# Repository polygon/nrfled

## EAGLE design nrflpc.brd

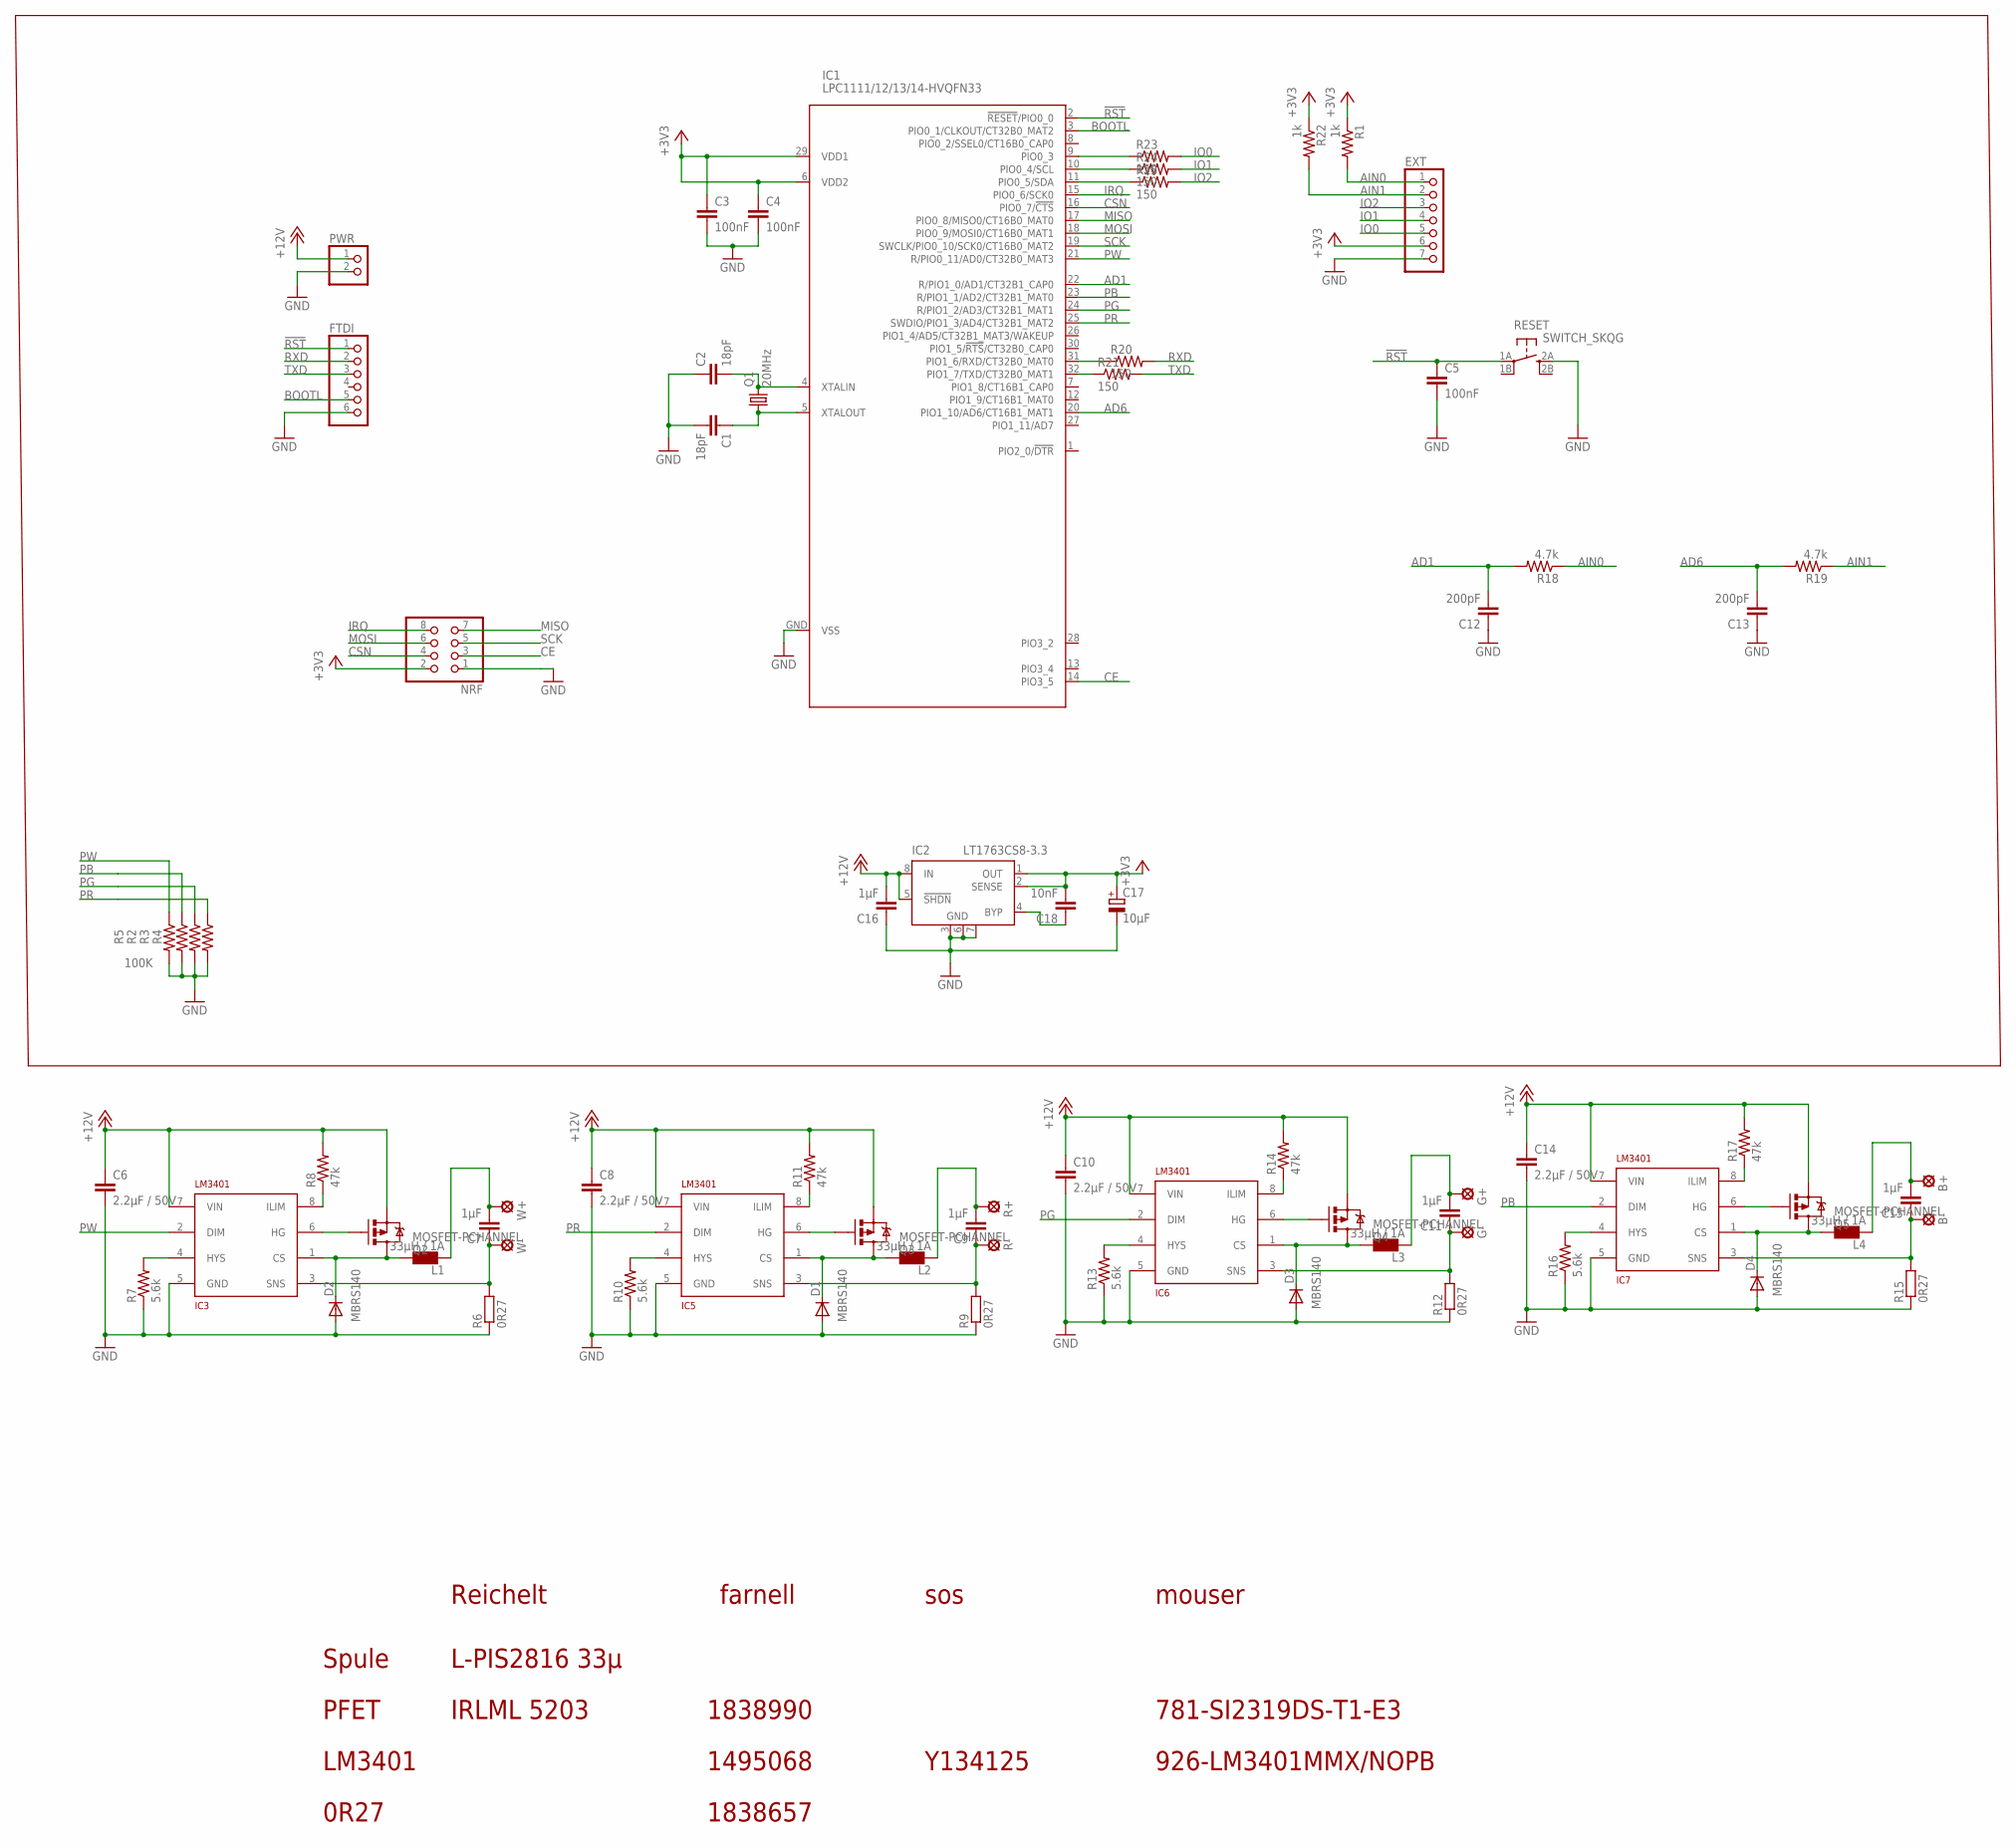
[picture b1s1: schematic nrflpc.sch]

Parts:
B+: SE14
B-: SE14
C1, C2: 18pF; 0402-CAP
C3, C4, C5: 100nF; 0402-CAP
C6, C8, C10, C14: 2.2µF / 50V; C1210
C7, C9, C11, C15, C16: 1µF; 0805
C12, C13: 200pF; 0402-CAP
C17: 10µF; SMC_A
C18: 10nF; 0402-CAP
D1, D2, D3, D4: MBRS140; SMB
EXT: PINHD-1X7; 1X07
FTDI: PINHD-1X6; 1X06
G+: SE14
G-: SE14
IC1: LPC1111/12/13/14-HVQFN33; HVQFN33
IC2: LT1763CS8-3.3; SOIC8
IC3, IC5, IC6, IC7: LM3401; MSOP8
L1, L2, L3, L4: 33µH / 1A; PIS2816
NRF: PINHD-2X4; 2X04
PWR: PINHD-1X2; 1X02
Q1: 20MHz; MT
Q2, Q3, Q4, Q5: MOSFET-PCHANNEL; SOT23
R1, R22: 1k; 0402-RES
R2, R3, R4, R5: 100K; 0402-RES
R6, R9, R12, R15: 0R27; R1206
R7, R10, R13, R16: 5.6k; 0805
R8, R11, R14, R17: 47k; 0805
R18, R19: 4.7k; 0402-RES
R20, R21, R23, R24, R25: 150; 0402-RES
R+: SE14
R-: SE14
RESET: SWITCH_SKQG
W+: SE14
W-: SE14

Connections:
!RST: C5.1, FTDI.1, IC1.2 (!RESET!/PIO0_0), RESET.1A
+3V3: C3.1, C4.1, C17.+, C18.2, EXT.6, IC1.6 (VDD2), IC1.29 (VDD1), IC2.1 (OUT), IC2.2 (SENSE), NRF.2, R1.1, R22.1
+12V: C6.1, C8.1, C10.1, C14.1, C16.2, IC2.5 (!SHDN), IC2.8 (IN), IC3.7 (VIN), IC5.7 (VIN), IC6.7 (VIN), IC7.7 (VIN), PWR.1, Q2.2 (S), Q3.2 (S), Q4.2 (S), Q5.2 (S), R8.2, R11.2, R14.2, R17.2
AD1: C12.2, IC1.22 (R/PIO1_0/AD1/CT32B1_CAP0), R18.2
AD6: C13.2, IC1.20 (PIO1_10/AD6/CT16B1_MAT1), R19.2
AIN0: EXT.1, R1.2, R18.1
AIN1: EXT.2, R19.1, R22.2
BOOTL: FTDI.5, IC1.3 (PIO0_1/CLKOUT/CT32B0_MAT2)
CE: IC1.14 (PIO3_5), NRF.3
CSN: IC1.16 (PIO0_7/!CTS!), NRF.4
GND: C1.2, C2.1, C3.2, C4.2, C5.2, C6.2, C8.2, C10.2, C12.1, C13.1, C14.2, C16.1, C17.-, D1.A, D2.A, D3.A, D4.A, EXT.7, FTDI.6, IC1.GND (VSS), IC2.3 (GND), IC2.6 (GND), IC2.7 (GND), IC3.5 (GND), IC5.5 (GND), IC6.5 (GND), IC7.5 (GND), NRF.1, PWR.2, R2.2, R3.2, R4.2, R5.2, R6.1, R7.1, R9.1, R10.1, R12.1, R13.1, R15.1, R16.1, RESET.2A
IO0: EXT.5, R23.2
IO1: EXT.4, R24.2
IO2: EXT.3, R25.2
IRQ: IC1.15 (PIO0_6/SCK0), NRF.8
MISO: IC1.17 (PIO0_8/MISO0/CT16B0_MAT0), NRF.7
MOSI: IC1.18 (PIO0_9/MOSI0/CT16B0_MAT1), NRF.6
unnamed: C7.1, IC3.3 (SNS), R6.2, W-.MP
unnamed: C7.2, L1.P$2 (2), W+.MP
unnamed: D2.C, IC3.1 (CS), L1.P$1 (1), Q2.3 (D)
unnamed: C9.1, IC5.3 (SNS), R9.2, R-.MP
unnamed: IC3.4 (HYS), R7.2
unnamed: C9.2, L2.P$2 (2), R+.MP
unnamed: IC3.8 (ILIM), R8.1
unnamed: D1.C, IC5.1 (CS), L2.P$1 (1), Q3.3 (D)
unnamed: IC5.4 (HYS), R10.2
unnamed: IC3.6 (HG), Q2.1 (G)
unnamed: IC5.8 (ILIM), R11.1
unnamed: IC5.6 (HG), Q3.1 (G)
unnamed: C11.1, G-.MP, IC6.3 (SNS), R12.2
unnamed: C11.2, G+.MP, L3.P$2 (2)
unnamed: D3.C, IC6.1 (CS), L3.P$1 (1), Q4.3 (D)
unnamed: IC6.4 (HYS), R13.2
unnamed: IC6.8 (ILIM), R14.1
unnamed: C18.1, IC2.4 (BYP)
unnamed: C2.2, IC1.4 (XTALIN), Q1.3 (2)
unnamed: IC6.6 (HG), Q4.1 (G)
unnamed: B-.MP, C15.1, IC7.3 (SNS), R15.2
unnamed: B+.MP, C15.2, L4.P$2 (2)
unnamed: D4.C, IC7.1 (CS), L4.P$1 (1), Q5.3 (D)
unnamed: IC7.4 (HYS), R16.2
unnamed: IC7.8 (ILIM), R17.1
unnamed: IC7.6 (HG), Q5.1 (G)
unnamed: IC1.31 (PIO1_6/RXD/CT32B0_MAT0), R20.1
unnamed: C1.1, IC1.5 (XTALOUT), Q1.1
unnamed: IC1.32 (PIO1_7/TXD/CT32B0_MAT1), R21.1
unnamed: IC1.9 (PIO0_3), R23.1
unnamed: IC1.10 (PIO0_4/SCL), R24.1
unnamed: IC1.11 (PIO0_5/SDA), R25.1
PB: IC1.23 (R/PIO1_1/AD2/CT32B1_MAT0), IC7.2 (DIM), R2.1
PG: IC1.24 (R/PIO1_2/AD3/CT32B1_MAT1), IC6.2 (DIM), R3.1
PR: IC1.25 (SWDIO/PIO1_3/AD4/CT32B1_MAT2), IC5.2 (DIM), R4.1
PW: IC1.21 (R/PIO0_11/AD0/CT32B0_MAT3), IC3.2 (DIM), R5.1
RXD: FTDI.2, R20.2
SCK: IC1.19 (SWCLK/PIO0_10/SCK0/CT16B0_MAT2), NRF.5
TXD: FTDI.3, R21.2

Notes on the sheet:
Reichelt
Spule
L-PIS2816 33µ
PFET
LM3401
farnell
0R27
1838990
1838657
1495068
Y134125
sos
mouser
781-SI2319DS-T1-E3
926-LM3401MMX/NOPB
IRLML 5203

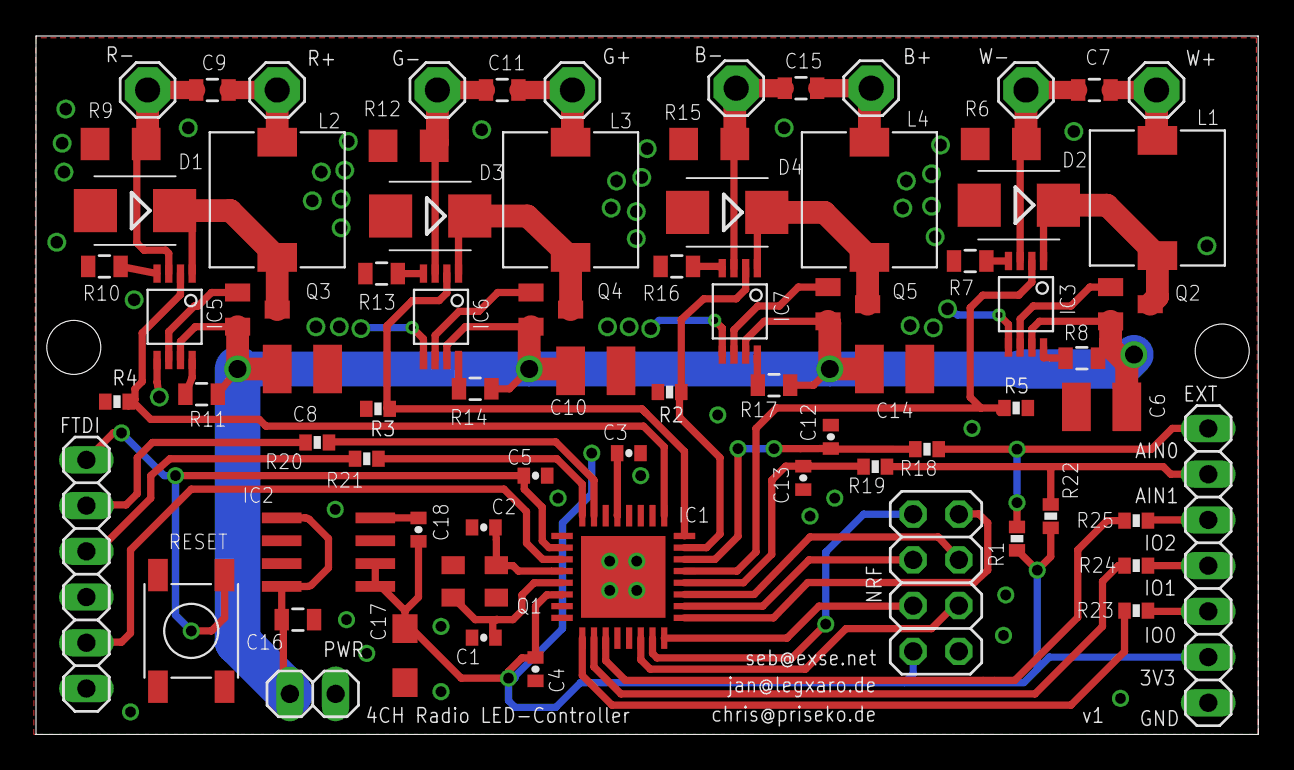
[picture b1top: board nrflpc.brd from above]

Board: 2 copper layers, 67.9 x 38.8 mm, 75 parts (0 on the bottom side), 56 nets.

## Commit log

2013-01-21 Initial
2013-01-21 Added nrfctrl
2013-01-24 Connectors for NRF-Module and FTDI
2013-01-24 More connections and extension connector
2013-01-27 Placement of parts, begin routing
2013-01-27 Eagle temp files to .gitignore
2013-01-27 LPC-Version of NRFLED
2013-01-27 Basic LPC circuitry for crystal and power
2013-01-28 Chosen good fitting PWM Pins, Reset circuitry
2013-01-28 Mostly final signal assignment, Starting to place
2013-01-29 ADC input filters
2013-01-29 UART series resistors
2013-01-29 Routing Power supply, in progress
2013-01-30 Layout
2013-01-30 Removed unnecessary pullups, new 3.3V regulator, begin routing
2013-01-31 Routing Voltage and "left" side (ISP)
2013-01-31 Almost final routing
2013-02-01 Fixed missing GND on IC2
2013-02-01 Fixed even more GND problems
    MORE GND!!!
2013-02-02 updated HVQFN33 package
2013-02-03 Compacting left side
2013-02-03 Compacted right side, reset switch added
2013-02-05 Labels and Makeup
2013-02-08 More silkscreen
2013-02-13 Silkscreen

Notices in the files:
parts and their libraries:
SparkFun-Resistors: Licensing: CC v3.0 Share-Alike You are welcome to use this library for commercial purposes.
